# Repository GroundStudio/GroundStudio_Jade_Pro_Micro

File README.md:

GroundStudio Jade Pro Micro
====================================

Get it from [ardushop.ro](https://ardushop.ro/ro/home/1731-jade-pro-micro.html)

Explore all the GroundStudio products at [GroundStudio.ro](https://groundstudio.ro/)

Description
-------------------
ATMEGA32U4 based development board with 32kBytes of In-System Self-Programmable Flash program memory, 1kBytes EEPROM, 2.5kBytes Internal SRAM, 5 PWM Channels, 18 Digital Pins and 9 channel 10 bit ADC Pins.

Contents
-------------------

* [/Documentation](https://github.com/GroundStudio/GroundStudio_Jade_Pro_Micro/tree/main/Documentation) -- Pinout.
* [/Hardware](https://github.com/GroundStudio/GroundStudio_Jade_Pro_Micro/tree/main/Hardware) -- Schematics, layout.

Versions
-------------------
*(Not all tags shown)*

- [REV 0.1]

License
-------------------

This is released under the [Attribution-ShareAlike 4.0 International (CC BY-SA 4.0)](https://creativecommons.org/licenses/by-sa/4.0/) license.
**You are welcome to use this for commercial purposes.**

Please consider contributing back to this project or others to help the open-source hardware community continue to thrive and grow! 

Certifications:

[Open Source Hardware Association](https://certification.oshwa.org/ro000004.html)   
   
[
](https://certification.oshwa.org/ro000004.html)

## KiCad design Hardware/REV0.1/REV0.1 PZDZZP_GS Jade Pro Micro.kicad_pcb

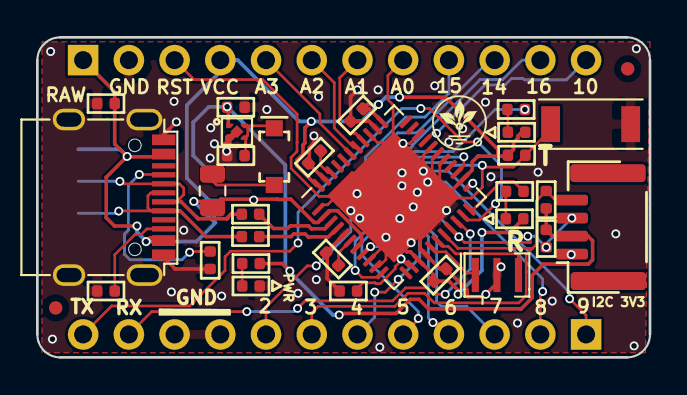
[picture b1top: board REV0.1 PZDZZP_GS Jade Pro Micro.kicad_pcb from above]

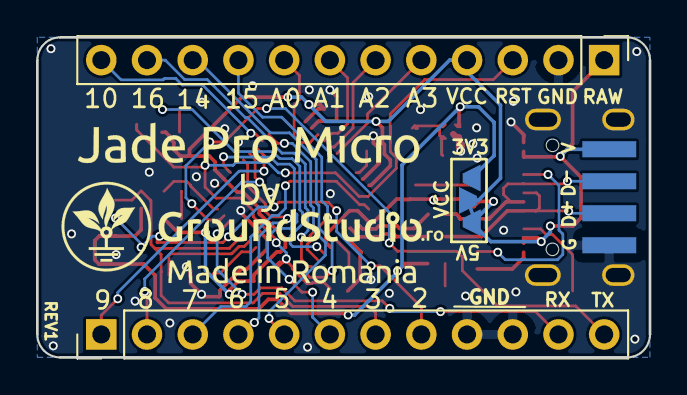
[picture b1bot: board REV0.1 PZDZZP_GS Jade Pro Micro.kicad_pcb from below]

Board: 2 copper layers, 34.0 x 17.8 mm, 33 parts (4 on the bottom side), 40 nets.

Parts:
C1, C2, C3, C4, C6, C7: 1uF; C_0402_1005Metric
C5, C8: 0.1uF; C_0402_1005Metric
D1: D_Schottky; SOD-123
F1: 6V 0.5A; Fuse_0805_2012Metric
J1: SolderJumper_DUAL_NC_1-3
J2, J3: Conn_01x12; PinHeader_1x12_P2.54mm_Vertical_Male
J5: Conn_01x04; USB-SOLDER-PADS
LED1, LED2, LED3: LED; LED_0402_1005Metric
R1, R2: 22; R_0402_1005Metric
R3, R4: 5.1k; R_0402_1005Metric
R5, R6, R7: 1k; R_0402_1005Metric
R8: 10k; R_0402_1005Metric
R9, R10: 2.2k; R_0402_1005Metric
SW2: SW_Push; TS342A2P-WZ
U1: ME6211C33U4AG-N; FBP1-1-4
U2: ATMEGA32U4-MUR; QFN-44-1EP_7x7mm_P0.5mm_EP5.15x5.15mm
USB1: USB_C_FULL; USB_C_C167321
X1: i2c_3V3; SH__1x04_P1.00mm_Horizontal
Y1: CSTNE16M0V530000R0; Resonator_SMD_muRata_CSTxExxG-3Pin_3.2x1.3mm

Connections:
+3V3: C2.1, J1.2, R5.1, R9.1, R10.1, U1.1, X1.2
A0: J3.8, U2.36
A1: J3.7, U2.37
A2: J3.6, U2.38
A3: J3.5, U2.39
AREF: C5.1, U2.42
D2-SDA: J2.8, R10.2, U2.19, X1.3
D3-SCL: J2.7, R9.2, U2.18, X1.4
D4: J2.6, U2.25
D5: J2.5, U2.31
D6: J2.4, U2.27
D7: J2.3, U2.1
D8: J2.2, U2.28
D9: J2.1, U2.29
D10: J3.12, U2.30
D+: J5.3, R2.2, USB1.A6, USB1.B6
D-: J5.2, R1.2, USB1.A7, USB1.B7
GND: C1.2, C2.2, C3.2, C4.2, C5.2, C6.2, C7.2, C8.2, J2.9, J2.10, J3.2, J5.4, LED1.1, R3.2, R4.2, SW2.1, U1.2, U1.5, U2.5, U2.15, U2.23, U2.35, U2.43, USB1.0, USB1.A1, USB1.A12, USB1.B1, USB1.B12, X1.1, Y1.2
MISO: J3.10, U2.11
MOSI: J3.11, U2.10
unnamed: C1.1, D1.1, U1.3, U1.4
unnamed: D1.2, F1.1
unnamed: LED1.2, R5.2
unnamed: LED2.1, R6.2
unnamed: LED3.1, R7.2
unnamed: R3.1, USB1.B5
unnamed: R4.1, USB1.A5
PB0: R7.1, U2.8
PD5: R6.1, U2.22
RESET: C4.1, J3.3, R8.2, SW2.2, U2.13
RXI: J2.11, U2.20
SCK: J3.9, U2.9
TXO: J2.12, U2.21
UCAP: C6.1, U2.6
UD+: R2.1, U2.4
UD-: R1.1, U2.3
VCC: C7.1, C8.1, J1.3, J3.4, LED2.2, LED3.2, R8.1, U2.14, U2.24, U2.34, U2.44
V_USB: C3.1, F1.2, J1.1, J3.1, J5.1, U2.2, U2.7, USB1.A4, USB1.A9, USB1.B4, USB1.B9
XTAL1: U2.17, Y1.3
XTAL2: U2.16, Y1.1

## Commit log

2022-08-11 - initial commit
2022-08-26 - added schematic pdf file
2022-08-26 - added "Kicad6" to revision folder name
2023-03-15 Update README.md
    - removed references to "library"
2023-11-03 - added datasheet
